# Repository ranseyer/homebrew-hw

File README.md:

View this project on [CADLAB.io](https://cadlab.io/project/22743). 

# homebrew-hw

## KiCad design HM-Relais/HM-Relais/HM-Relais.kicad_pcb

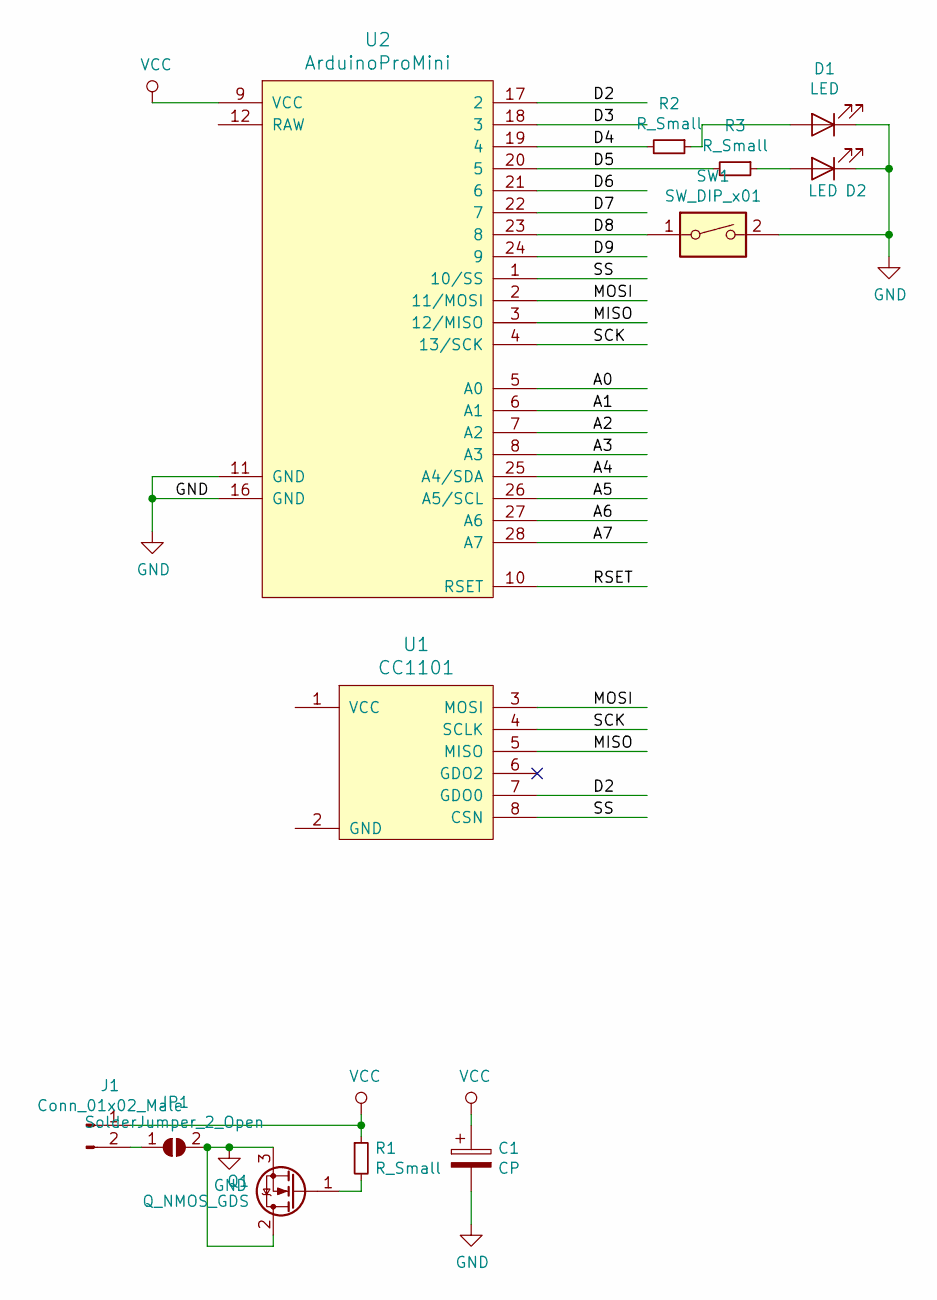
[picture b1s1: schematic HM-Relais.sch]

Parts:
C1: CP; CP_Axial_L10.0mm_D4.5mm_P15.00mm_Horizontal
D1, D2: LED; LED_D3.0mm
J1: Conn_01x02_Male; PinSocket_1x02_P2.54mm_Vertical
JP1: SolderJumper_2_Open; SolderJumper-2_P1.3mm_Open_Pad1.0x1.5mm
Q1: Q_NMOS_GDS; TO-251-3_Vertical
R1, R2, R3: R_Small; R_Axial_DIN0207_L6.3mm_D2.5mm_P5.08mm_Vertical
SW1: SW_DIP_x01; SW_SPST_CK_RS282G05A3
U1: CC1101; CC1101_SMD_THT
U2: ArduinoProMini

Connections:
/A0: U2.5 (A0)
/A1: U2.6 (A1)
/A2: U2.7 (A2)
/A3: U2.8 (A3)
/A4: U2.25 (A4/SDA)
/A5: U2.26 (A5/SCL)
/A6: U2.27 (A6)
/A7: U2.28 (A7)
/D2: U1.7 (GDO0), U2.17 (2)
/D3: U2.18 (3)
/D4: R2.2, U2.19 (4)
/D5: R3.2, U2.20 (5)
/D6: U2.21 (6)
/D7: U2.22 (7)
/D8: SW1.1, U2.23 (8)
/D9: U2.24 (9)
/MISO: U1.5 (MISO), U2.3 (12/MISO)
/MOSI: U1.3 (MOSI), U2.2 (11/MOSI)
/RSET: U2.10 (RSET)
/SCK: U1.4 (SCLK), U2.4 (13/SCK)
/SS: U1.8 (CSN), U2.1 (10/SS)
GND: C1.2, D1.1 (K), D2.1 (K), JP1.2 (B), Q1.2 (D), Q1.3 (S), SW1.2, U2.11 (GND), U2.16 (GND)
unnamed: D1.2 (A), R2.1
unnamed: D2.2 (A), R3.1
unnamed: J1.2, JP1.1 (A)
unnamed: Q1.1 (G), R1.2
VCC: C1.1, J1.1, R1.1, U2.9 (VCC)

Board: 2 copper layers, 12 parts (0 on the bottom side), 14 nets, no tracks yet.

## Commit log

2019-06-04 RC-8
2019-06-06 Remote
2019-08-03 Doku
2019-10-26 V03, Pics
2019-12-29 docs
2020-01-12 HM Relais
2020-02-07 Relais
2020-04-01 Backlink to CADLAB.io has been added.
2020-06-28 Sketch
2021-04-12 Moved Homematic projects
